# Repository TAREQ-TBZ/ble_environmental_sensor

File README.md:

# Environmental Sensor - BLE

A BLE environmental sensor firmware built on [Zephyr RTOS](https://www.zephyrproject.org/) v4.3.0. Measures temperature and humidity using a Sensirion SHT4x sensor and transmits readings over Bluetooth Low Energy (Environmental Sensing Service).

The Zigbee version can be found at: https://github.com/TAREQ-TBZ/environmental_sensor

## Key Features

- **Ultra-low power** - ~6 uA connected, ~11 uA advertising, powered by CR2032 coin cell
- **BLE peripheral** with Environmental Sensing Service (temperature + humidity notifications)
- **OTA DFU** via MCUboot + MCUmgr over BLE
- **Custom PCB** with nRF52833 + SHT40 + 2.45 GHz PCB monopole antenna

| Board top side | Board bottom side |
|---|---|
|  |  |

### Current consumption

| Advertising | Connected |
|---|---|
|  |  |

## Supported Boards

| Board | Type | Description |
|---|---|---|
| `sham_nrf52833` | Custom board | Target hardware (nRF52833 + SHT40). Full support including MCUboot OTA. |
| `esp32s3_devkitc/esp32s3/procpu` | Dev board | ESP32-S3 DevKitC with SHT3xD sensor for development/testing. |

## Getting Started

There are two ways to set up the development environment:

1. **VS Code Dev Container** (recommended) - all toolchains and dependencies pre-installed
2. **Manual setup** - install Zephyr SDK and tools on your host machine

### Option 1: VS Code Dev Container

**Prerequisites:** [Docker](https://docs.docker.com/get-docker/) and [VS Code](https://code.visualstudio.com/) with the [Dev Containers](https://marketplace.visualstudio.com/items?itemName=ms-vscode-remote.remote-containers) extension.

1. Clone the repository:
   ```shell
   git clone git@github.com:TAREQ-TBZ/ble_environmental_sensor.git
   ```

2. Open the repository folder in VS Code:
   ```shell
   code ble_environmental_sensor
   ```

3. When prompted **"Reopen in Container"**, click yes. Or use the command palette: `Dev Containers: Rebuild and Reopen in Container`.

4. Wait for the container to build. On first run this downloads the Zephyr SDK, toolchains, and all Zephyr modules (~20 min depending on network speed). Subsequent starts are instant.

5. Build from the VS Code terminal:
   ```shell
   west build -p always -b sham_nrf52833 app
   ```

The container mounts the repository at `/home/vscode/application` and uses its `west.yml` directly as the west workspace manifest. All Zephyr modules, toolchains (ARM, RISC-V, Xtensa), and host tools are pre-installed.

> **Building the container image locally:** The `devcontainer.json` defaults to a pre-built image. To build locally (e.g., to customize toolchains), uncomment the `"build"` section in `.devcontainer/devcontainer.json` and comment out the `"image"` line.

### Option 2: Manual Setup (Terminal)

**Prerequisites:** Linux host with Python 3.10+, `cmake`, `ninja-build`, `git`, `device-tree-compiler`, and the [Zephyr SDK](https://docs.zephyrproject.org/latest/develop/getting_started/index.html).

```shell
# Create workspace and virtual environment
mkdir ws && cd ws
python3 -m venv .venv
source .venv/bin/activate
pip install west

# Initialize workspace from the application manifest
west init -m git@github.com:TAREQ-TBZ/ble_environmental_sensor.git --mr main
west update
pip install -r zephyr/scripts/requirements.txt

# For ESP32 targets: fetch required binary blobs
west blobs fetch hal_espressif

# Build
west build -b sham_nrf52833 application/app
```

> **Note:** When using the manual setup, build commands run from the workspace root (`ws/`) and the application path is `application/app`. In the Dev Container, you are already inside the `application/` directory, so the path is just `app`.

## Building

All build commands below assume you are inside the Dev Container or in the `application/` directory. When using the manual setup from the workspace root, replace `app` with `application/app`.

### sham_nrf52833 (Target Hardware)

```shell
# Standard build
west build -p always -b sham_nrf52833 app

# With MCUboot bootloader (required for OTA DFU)
west build -p always --sysbuild -b sham_nrf52833 app

# Debug build (enables UART logging at 115200 baud)
west build -p always -b sham_nrf52833 app -DEXTRA_CONF_FILE=debug.conf
```

### ESP32-S3 DevKitC

```shell
west build -p always -b esp32s3_devkitc/esp32s3/procpu app
```

The board overlay at `app/boards/esp32s3_devkitc_esp32s3_procpu.overlay` defines the LED pin and SHT3xD sensor for this dev board.

## Flashing

### sham_nrf52833

The default flash runner is `nrfjprog`. Supported runners: `nrfjprog`, `nrfutil`, `jlink`, `pyocd`, `openocd`.

```shell
# Flash using the default runner (nrfjprog)
west flash

# Or specify a runner explicitly
west flash -r jlink
west flash -r openocd
```

When using sysbuild, specify the app domain to flash the application (MCUboot + app are both flashed):

```shell
west flash -d build
```

> **J-Link:** Requires [SEGGER J-Link](https://www.segger.com/downloads/jlink/) installed on the host. In the Dev Container, it is bind-mounted from `/opt/SEGGER/JLink`.

### ESP32-S3 DevKitC

```shell
# Flash over USB
west flash -r esp32

# Monitor serial output
west espressif monitor
```

## OTA DFU (Over-The-Air Firmware Update)

The firmware supports OTA updates via MCUmgr over BLE when built with `--sysbuild` (which includes MCUboot).

Build with sysbuild to produce a signed firmware image:

```shell
west build -p always --sysbuild -b sham_nrf52833 app
```

The signed application image is at `build/app/zephyr/zephyr.signed.bin`. Use any MCUmgr-compatible client (e.g., the [nRF Connect](https://www.nordicsemi.com/Products/Development-tools/nRF-Connect-for-mobile) mobile app or the [mcumgr CLI](https://docs.zephyrproject.org/latest/services/device_mgmt/mcumgr.html)) to upload the image over BLE.

## Configuration

Application-specific Kconfig options are defined in `app/Kconfig`:

| Option | Default | Description |
|---|---|---|
| `CONFIG_MEASURING_PERIOD_SECONDS` | 30 | Sensor sampling interval (seconds) |
| `CONFIG_FIRST_MEASUREMENT_DELAY_SECONDS` | 10 | Delay before first measurement after boot |
| `CONFIG_MIN_ADV_INTERVAL_MS` | 500 | Minimum BLE advertising interval (ms) |
| `CONFIG_MAX_ADV_INTERVAL_MS` | 501 | Maximum BLE advertising interval (ms) |

Override at build time:

```shell
west build -p always -b sham_nrf52833 app -DCONFIG_MEASURING_PERIOD_SECONDS=60
```

## Code Formatting

CI enforces formatting on all pull requests.

```shell
# C code (uses .clang-format: LLVM-based, 8-space tabs, 100-column limit)
clang-format -i app/src/*.c app/src/*.h

# Python
black systemtest/
```

## Hardware

The KiCad design files (schematic, PCB, BOM) are in `Hardware_files/sham_nrf52833/`.

Key components:
- Nordic nRF52833 (QDAA package)
- Sensirion SHT40 temperature/humidity sensor (I2C, address 0x44)
- 2.45 GHz PCB monopole antenna
- CR2032 coin cell holder
- Status LED + user button

## License

This project is licensed under the Apache License 2.0. See [LICENSE](LICENSE) for details.

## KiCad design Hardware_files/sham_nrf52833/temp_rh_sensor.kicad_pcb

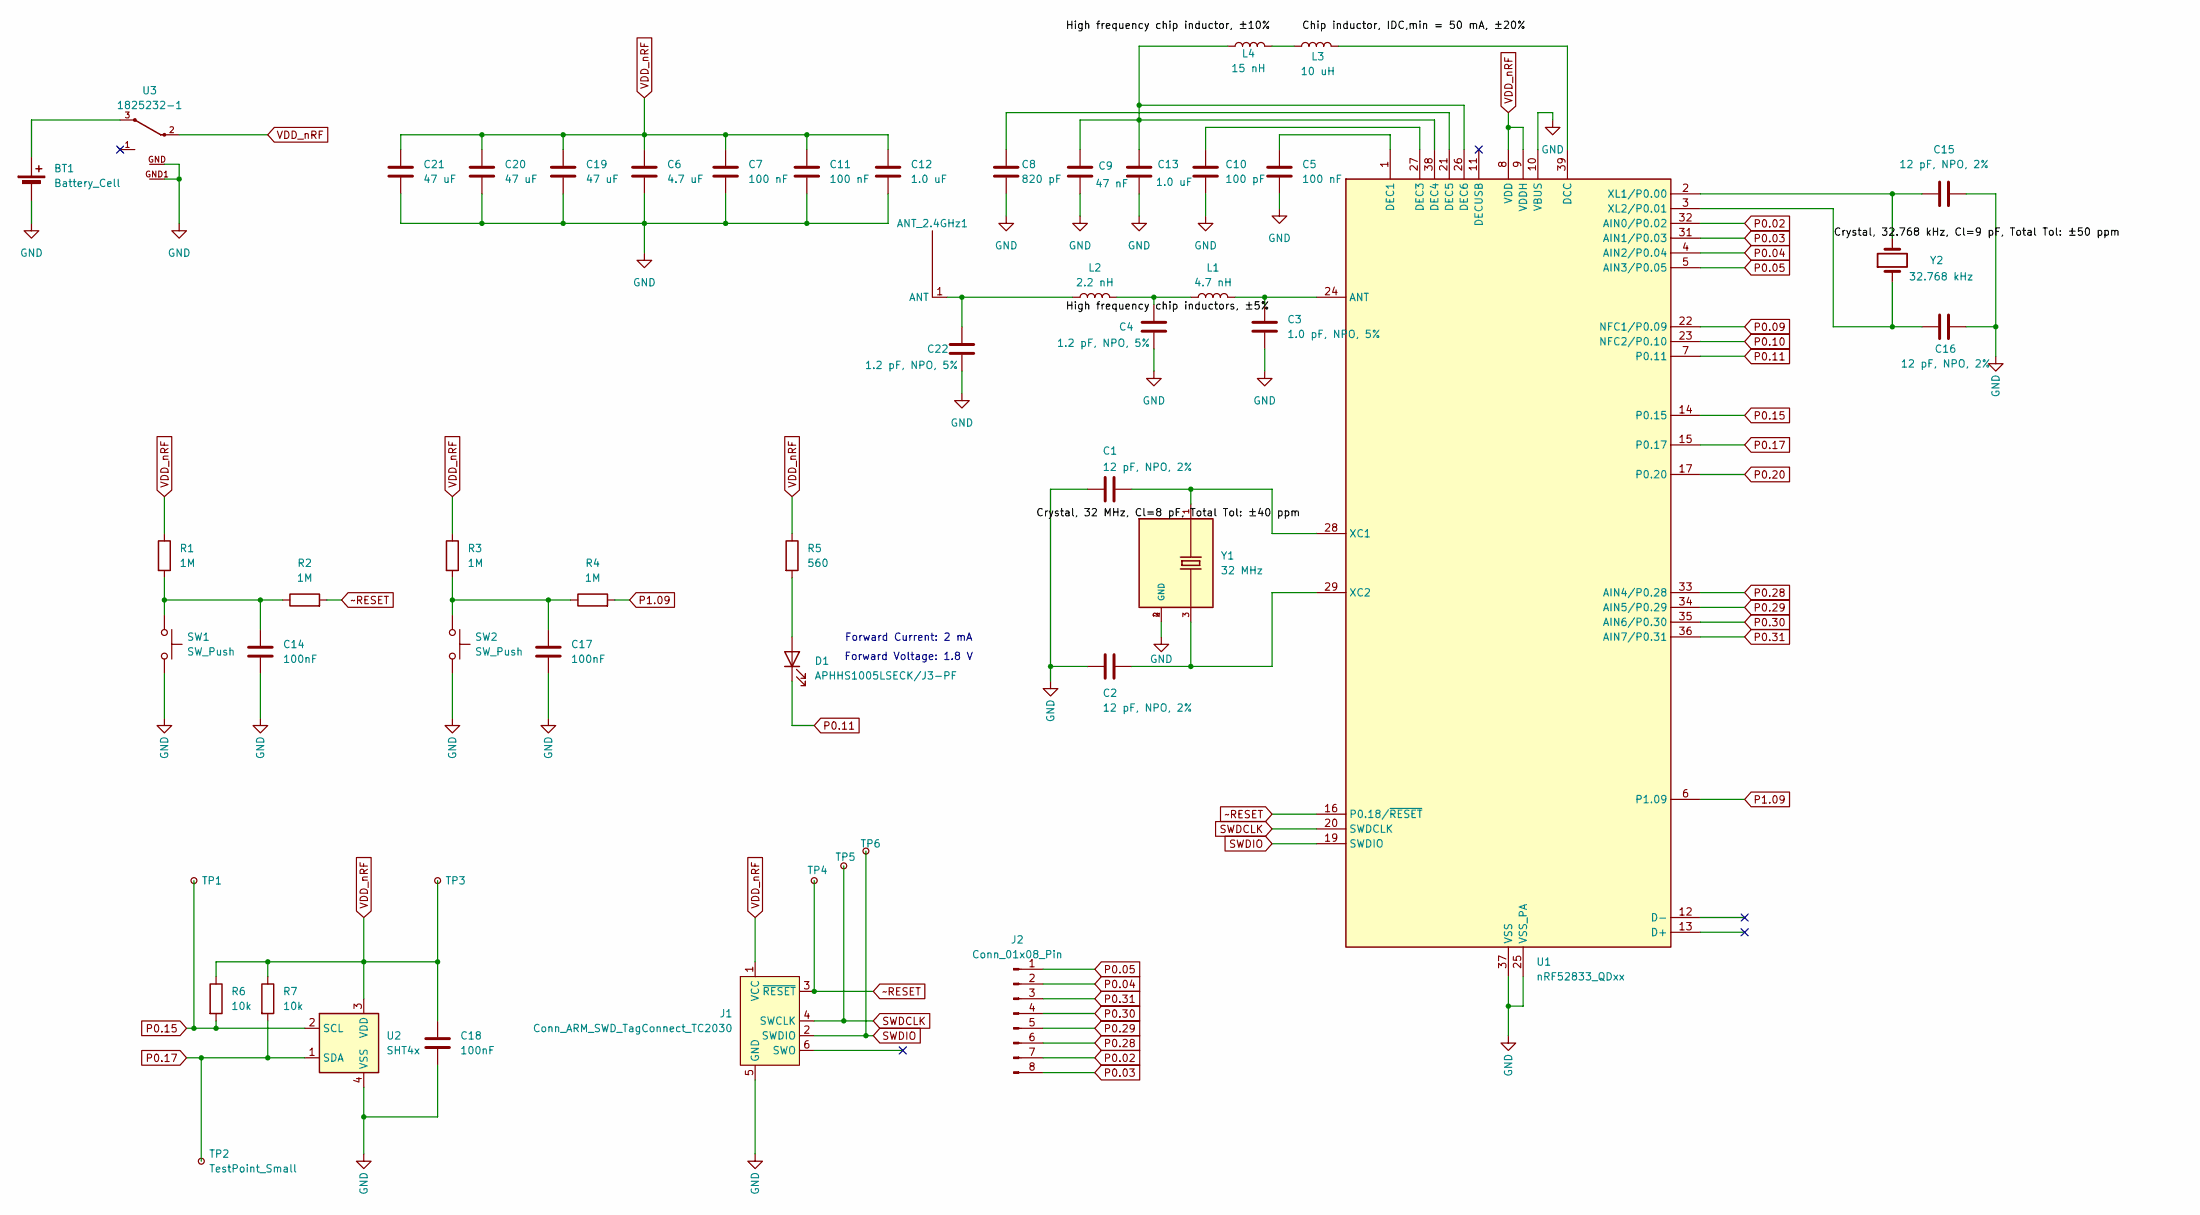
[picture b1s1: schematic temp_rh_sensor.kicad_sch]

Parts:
ANT_2.4GHz1: antenna_2_4GHz
BT1: Battery_Cell; RENATA_SMTU2032-1
C1, C2, C15, C16: 12 pF, NPO, 2%; C_0402_1005Metric
C3: 1.0 pF, NPO, 5%; C_0402_1005Metric
C4, C22: 1.2 pF, NPO, 5%; C_0402_1005Metric
C5, C7, C11: 100 nF; C_0402_1005Metric
C6: 4.7 uF; C_0603_1608Metric
C8: 820 pF; C_0402_1005Metric
C9: 47 nF; C_0402_1005Metric
C10: 100 pF; C_0402_1005Metric
C12, C13: 1.0 uF; C_0402_1005Metric
C14, C17, C18: 100nF; C_0402_1005Metric
C19, C20, C21: 47 uF; C_0603_1608Metric
D1: APHHS1005LSECK/J3-PF; LED_0402_1005Metric
J1: Conn_ARM_SWD_TagConnect_TC2030; Tag-Connect_TC2030-IDC-FP_2x03_P1.27mm_Vertical
J2: Conn_01x08_Pin; PinHeader_1x08_P2.54mm_Vertical_SMD_Pin1Right
L1: 4.7 nH; L_0402_1005Metric
L2: 2.2 nH; L_0402_1005Metric
L3: 10 uH; L_0603_1608Metric
L4: 15 nH; L_0402_1005Metric
R1, R2, R3, R4: 1M; R_0402_1005Metric
R5: 560; R_0402_1005Metric
R6, R7: 10k; R_0402_1005Metric
SW1, SW2: SW_Push; SW_Push_1P1T_XKB_TS-1187A
TP1, TP2, TP3, TP4, TP5, TP6: TestPoint_Small; TestPoint_Pad_D1.0mm
U1: nRF52833_QDxx; QFN-40-1EP_5x5mm_P0.4mm_EP3.6x3.6mm
U2: SHT4x; Sensirion_DFN-4_1.5x1.5mm_P0.8mm_SHT4x_NoCentralPad
U3: 1825232-1
Y1: 32 MHz; OSCCC320X250X60N; PARTREV N/A
Y2: 32.768 kHz; Crystal_SMD_3215-2Pin_3.2x1.5mm

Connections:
/Crystal, 32.768 kHz, Cl=9 pF, Total Tol: ±50 ppm: C16.1, U1.3 (XL2/P0.01), Y2.1
GND: BT1.2 (-), C1.2, C2.2, C3.2, C4.2, C5.2, C6.2, C7.2, C8.2, C9.2, C10.2, C11.2, C12.2, C13.2, C14.2, C15.2, C16.2, C17.2, C18.2, C19.2, C20.2, C21.2, C22.2, J1.5 (GND), SW1.2, SW2.2, U1.10 (VBUS), U1.25 (VSS_PA), U1.37 (VSS), U1.41 (VSS), U2.4 (VSS), U3.GND, U3.GND1, Y1.2 (GND), Y1.4 (GND)
unnamed: ANT_2.4GHz1.1 (ANT), C22.1, L2.1
unnamed: BT1.1 (+), U3.3
unnamed: C4.1, L1.1, L2.2
unnamed: C14.1, R1.2, R2.1, SW1.1
unnamed: C17.1, R3.2, R4.1, SW2.1
unnamed: D1.2 (A), R5.2
unnamed: L3.1, L4.2
unnamed: C3.1, L1.2, U1.24 (ANT)
unnamed: L3.2, U1.39 (DCC)
unnamed: C5.1, U1.1 (DEC1)
unnamed: C10.1, U1.27 (DEC3)
unnamed: C9.1, C13.1, L4.1, U1.26 (DEC6), U1.38 (DEC4)
unnamed: C8.1, U1.21 (DEC5)
unnamed: C1.1, U1.28 (XC1), Y1.1
unnamed: C2.1, U1.29 (XC2), Y1.3
unnamed: C15.1, U1.2 (XL1/P0.00), Y2.2
P0.02: J2.7, U1.32 (AIN0/P0.02)
P0.03: J2.8, U1.31 (AIN1/P0.03)
P0.04: J2.2, U1.4 (AIN2/P0.04)
P0.05: J2.1, U1.5 (AIN3/P0.05)
P0.09: U1.22 (NFC1/P0.09)
P0.10: U1.23 (NFC2/P0.10)
P0.11: D1.1 (K), U1.7 (P0.11)
P0.15: R6.2, TP1.1, U1.14 (P0.15), U2.2 (SCL)
P0.17: R7.2, TP2.1, U1.15 (P0.17), U2.1 (SDA)
P0.20: U1.17 (P0.20)
P0.28: J2.6, U1.33 (AIN4/P0.28)
P0.29: J2.5, U1.34 (AIN5/P0.29)
P0.30: J2.4, U1.35 (AIN6/P0.30)
P0.31: J2.3, U1.36 (AIN7/P0.31)
P1.09: R4.2, U1.6 (P1.09)
SWDCLK: J1.4 (SWCLK), TP5.1, U1.20 (SWDCLK)
SWDIO: J1.2 (SWDIO), TP6.1, U1.19 (SWDIO)
VDD_nRF: C6.1, C7.1, C11.1, C12.1, C18.1, C19.1, C20.1, C21.1, J1.1 (VCC), R1.1, R3.1, R5.1, R6.1, R7.1, TP3.1, U1.8 (VDD), U1.9 (VDDH), U1.18 (VDD), U1.30 (VDD), U1.40 (VDD), U2.3 (VDD), U3.2
~RESET: J1.3 (~RESET), R2.2, TP4.1, U1.16 (P0.18/~RESET)

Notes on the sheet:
Forward Voltage: 1.8 V
Forward Current: 2 mA

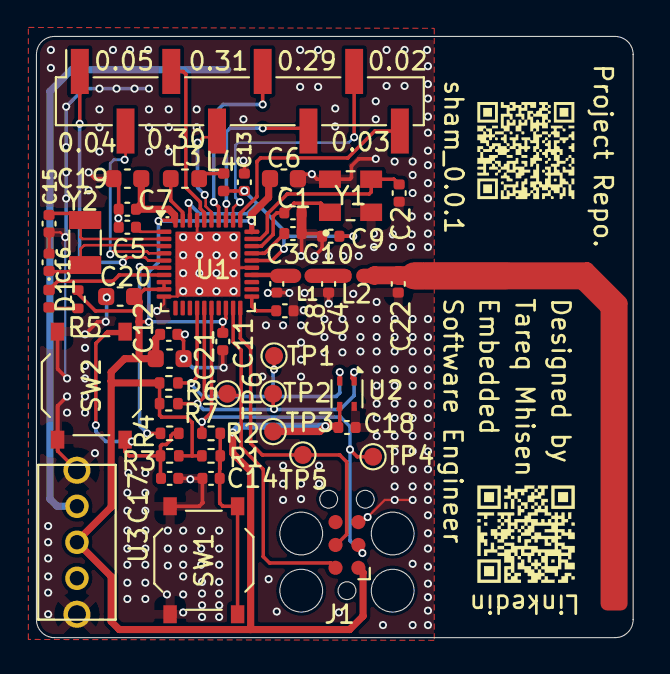
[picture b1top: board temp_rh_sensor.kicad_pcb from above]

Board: 2 copper layers, 33.2 x 33.4 mm, 51 parts (1 on the bottom side), 34 nets.

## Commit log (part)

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2025-02-17 app: add minimal zephyr app skeleton
2025-02-17 app: send the measuremnets over ble
2025-02-17 app: add user interface module
    This commit introduces the user interface service, which handles LED
    indicators and button inputs.
2025-02-17 boards: add sham_nrf52833 board
    sham_nrf52833 is the main board used for this project.
2025-02-17 app: add ble service
2025-02-17 clang-format: add support for clang-format
    Copied from latest upstream Zephyr version, as of commit 64492b6
    You can call "clang-format -style=file -i my_src.c" within the repo
    to in-place fix the style.
2025-02-17 app: trigger periodic measurements (hum. & temp.)
2025-02-17 app: add humidity & temperature service
    This change introduces the humidity and temperature sensor service,
    responsible for interfacing with the sensor. The service provides
    functions to read and process environmental data, which can then be
    transmitted over Zigbee.
2025-02-17 app: add events service
2025-02-17 README: add project description
2025-02-17 app: use user interface service in main
2025-02-17 app: disable logging to save power
2025-02-17 ci: add workflows for code formatting and build checks
2025-02-23 app: disable logging in production code to save power
    Logging is now activated for debugging using debug.conf configuration.
2025-02-26 systemtest: test ble functionality of the device
2025-02-26 app: allow updating app image over ble
2025-02-26 app: log firmware version on startup
2025-02-27 ci: adjust build archive to also include dfu image
2025-02-27 fix systemtest
2025-02-27 ci: build a debug image
2025-02-27 fix pull
2025-02-27 systemtest: add list of required package
2025-02-27 ci: trigger hardware in the loop test on each PR
2025-02-27 fix build
2026-01-28 ble_svc: fix bt_conn lifetime bug and replace mutex with atomics
    Fix a potential use-after-free bug where bt_conn pointer was stored
    without proper reference counting. The connection could be freed by
    the BLE stack between reading the pointer and using it for notification.
    Changes:
    - Add bt_conn_ref() in on_connected to take ownership of connection
    - Add bt_conn_unref() in on_disconnected to release the reference
2026-01-28 Migrate to nRF Connect SDK v3.2.1
    Update from nRF Connect SDK v2.8.0 to v3.2.1 with the following changes:
    SDK Version:
    - Update west.yml revision from v2.8.0 to v3.2.1
    Board Definition (HWMv1 -> HWMv2):
    - Move board from boards/arm/sham_nrf52833/ to boards/sham_TBZ/sham_nrf52833/
    - Rename Kconfig.sham_nrf52833 to Kconfig
2026-02-15 app: apply embedded design patterns refactoring
    - Callback pattern: Replace raw function pointer in user_interface with
    struct-based callback (ui_button_callback) using CONTAINER_OF for
    type-safe context recovery in the handler
    - Return value pattern: Change ble_svc_init() and
    ble_svc_increase_button_press_cnt() to return int with proper error
    propagation. Change humidity_temperature_svc get_temperature/humidity
2026-02-15 fix: update board.yml and prj.conf for NCS v3.2.1 compatibility
    Remove unsupported keys (full_name, variants) from board.yml that are
    not in the SDK v3.2.1 board schema, and remove undefined Kconfig symbol
    CONFIG_SETTINGS_ZMS_LEGACY from prj.conf.
2026-02-15 refactor: convert humidity_temperature_svc from singleton to object pattern
    Replace the singleton pattern (static struct + file-scoped device pointer)
    with the object pattern, where all state is passed explicitly via a `self`
    pointer.
    Why:
    The singleton pattern coupled the service implementation to a single,
    compile-time-fixed sensor instance. The static `DEVICE_DT_GET_ONE` macro
2026-02-22 refactor: replace event bus with callback pattern across all modules
    Replace the events_svc message queue (event bus pattern) with the
    callback/observer pattern throughout the application. This demonstrates
    all callback pattern possibilities from Martin Schroder's design patterns:
    struct-based callbacks, CONTAINER_OF context recovery, one-to-many via
    sys_slist_t, multiple ops per struct, work queue deferral, and full
    decoupling between modules.
2026-02-23 add Callback-Pattern-vs-Event-Bus-vs-Zbus.md
2026-03-28 migrate to nRF Connect SDK v3.2.1
    Update from nRF Connect SDK v2.8.0 to v3.2.1 with the following changes:
    SDK Version:
    - Update west.yml revision from v2.8.0 to v3.2.1
    Board Definition (HWMv1 -> HWMv2):
    - Move board from boards/arm/sham_nrf52833/ to boards/sham_TBZ/sham_nrf52833/
    - Rename Kconfig.sham_nrf52833 to Kconfig
2026-03-28 boards: enable CONFIG_HW_STACK_PROTECTION conditionally
    All Nordic boards were enabling CONFIG_HW_STACK_PROTECTION
    unconditionally, which is usually not a problem except if the particular
    application happens to want to disable the MPU (or equivalent hardware
    for RISC-V). In that case, the following warning is shown:
    warning: HW_STACK_PROTECTION (defined at arch/Kconfig) was assigned the
    value 'y' but got the value 'n'.
2026-03-28 boards: delete deprecated BT_CTLR
    see:
    https://github.com/zephyrproject-rtos/zephyr/commit/8b02141ca77f087c65b5067f571758c2b7e5b6e2
2026-03-28 ble_svc: stop using deprecated macros and variables
    use le.interval_us instead of deprecated le.interval.
    use BT_LE_ADV_OPT_CONN instead of deprecated BT_LE_ADV_OPT_CONNECTABLE.
2026-03-28 migrate to vanilla zephyr rtos v4.3.0
2026-03-28 add support for esp32 s3 devkitc board
2026-03-28 ble_svc: fix connection interval calculation for Zephyr v4.3.0
    bt_conn_le_info.interval_us was removed in vanilla Zephyr. Use
    the standard interval field with CONNECTION_INTERVAL_UNIT_MS instead.
2026-03-28 boards: move board definitions into app/boards/
    Move custom board files and overlays from the repo root boards/
    directory into app/boards/. This places them under APPLICATION_SOURCE_DIR
    so Zephyr discovers both board definitions and application overlays
    from a single location.
    Update zephyr/module.yml board_root from "." to "app" to match.
    The esp32s3 overlay now also defines the status LED (gpio0 pin 38)
2026-03-28 add plan to move to zbus
2026-03-28 add devcontainer based development setup
2026-03-28 ble_svc: use BT_LE_ADV_OPT_CONN instead of deprecated BT_LE_ADV_OPT_CONNECTABLE.
